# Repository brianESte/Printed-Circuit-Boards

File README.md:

# Printed-Circuit-Boards
A collection of PCBs. Most are interface boards between breadboard and some kind of non-breadboard friendly package.

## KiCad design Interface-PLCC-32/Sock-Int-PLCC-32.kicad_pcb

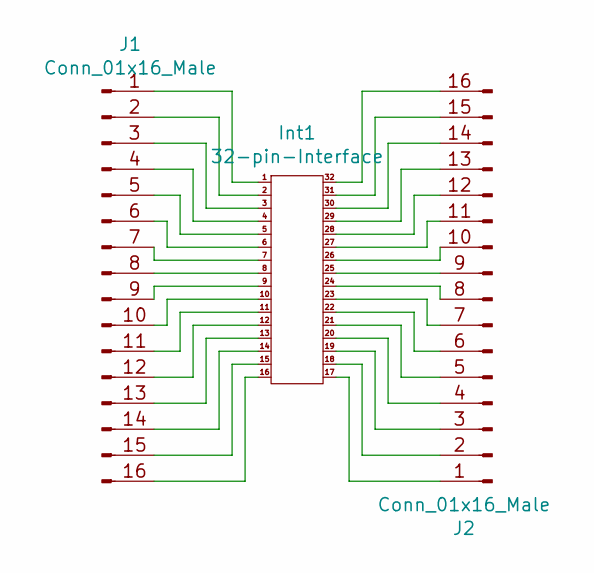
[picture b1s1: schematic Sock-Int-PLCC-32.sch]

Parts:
Int1: 32-pin-Interface; PLCC-Socket-32
J1, J2: Conn_01x16_Male; PinHeader_1x16_P2.54mm_Vertical

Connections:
unnamed: Int1.1, J1.1
unnamed: Int1.2, J1.2
unnamed: Int1.3, J1.3
unnamed: Int1.4, J1.4
unnamed: Int1.5, J1.5
unnamed: Int1.6, J1.6
unnamed: Int1.7, J1.7
unnamed: Int1.8, J1.8
unnamed: Int1.9, J1.9
unnamed: Int1.10, J1.10
unnamed: Int1.11, J1.11
unnamed: Int1.12, J1.12
unnamed: Int1.13, J1.13
unnamed: Int1.14, J1.14
unnamed: Int1.15, J1.15
unnamed: Int1.16, J1.16
unnamed: Int1.17, J2.1
unnamed: Int1.18, J2.2
unnamed: Int1.19, J2.3
unnamed: Int1.20, J2.4
unnamed: Int1.21, J2.5
unnamed: Int1.22, J2.6
unnamed: Int1.23, J2.7
unnamed: Int1.24, J2.8
unnamed: Int1.25, J2.9
unnamed: Int1.26, J2.10
unnamed: Int1.27, J2.11
unnamed: Int1.28, J2.12
unnamed: Int1.29, J2.13
unnamed: Int1.30, J2.14
unnamed: Int1.31, J2.15
unnamed: Int1.32, J2.16

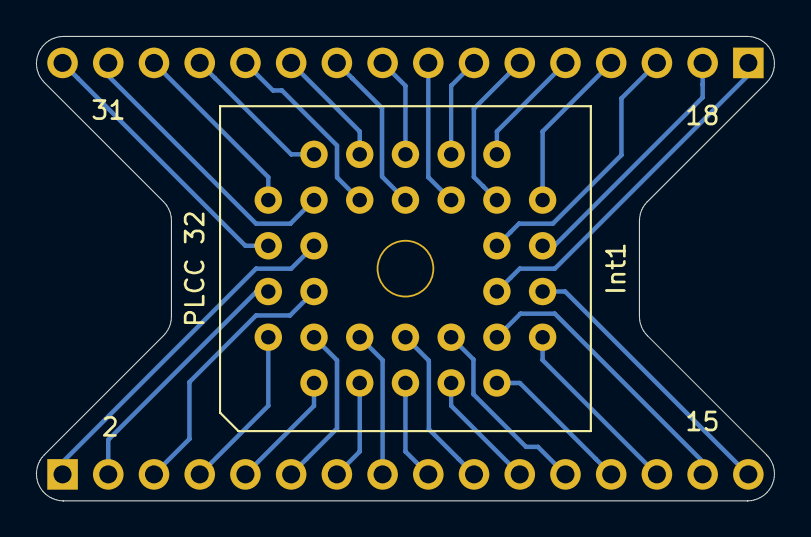
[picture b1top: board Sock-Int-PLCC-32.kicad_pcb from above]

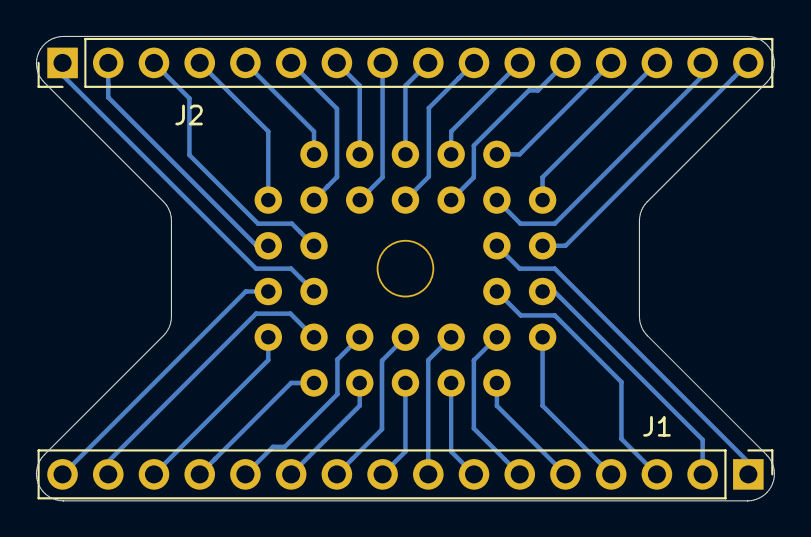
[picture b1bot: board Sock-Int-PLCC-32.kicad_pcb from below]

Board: 2 copper layers, 41.0 x 25.8 mm, 3 parts (2 on the bottom side), 32 nets.

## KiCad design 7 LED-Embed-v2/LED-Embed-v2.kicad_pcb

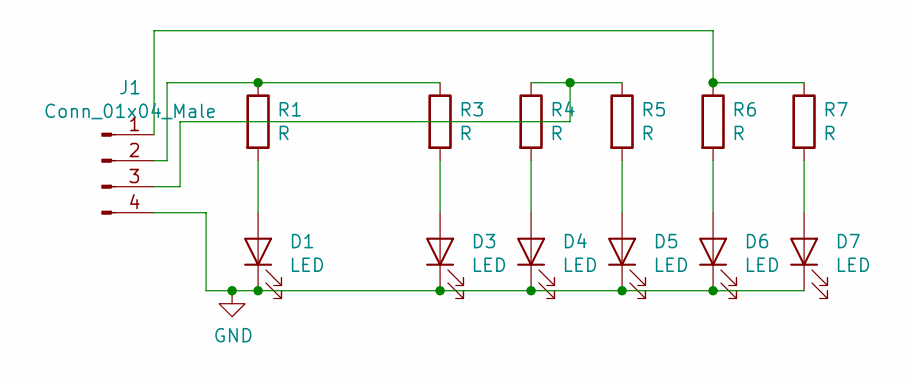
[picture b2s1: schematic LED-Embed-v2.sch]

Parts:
D1: LED; RaisedDome-3.2x1.85
D3: LED; CylLens-3.2x1.1
D4: LED; FlatTop-3.2x0.75
D5, D6: LED; RaisedDome-3.0x2.8
D7: LED; SlantedDome-3.2x1.6
J1: Conn_01x04_Male; PinHeader_1x04_P2.54mm_Vertical
R1, R3, R4, R5, R6, R7: R; R_0805_2012Metric

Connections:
GND: D1.1 (K), D3.1 (K), D4.1 (K), D5.1 (K), D6.1 (K), D7.1 (K), J1.4
unnamed: D1.2 (A), R1.2
unnamed: D3.2 (A), R3.2
unnamed: D4.2 (A), R4.2
unnamed: D5.2 (A), R5.2
unnamed: D6.2 (A), R6.2
unnamed: D7.2 (A), R7.2
unnamed: J1.1, R6.1, R7.1
unnamed: J1.2, R1.1, R3.1
unnamed: J1.3, R4.1, R5.1

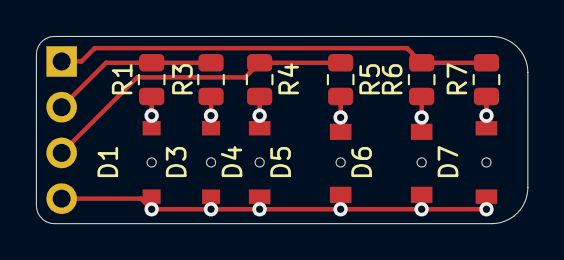
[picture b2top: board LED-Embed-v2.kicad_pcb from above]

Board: 2 copper layers, 27.3 x 10.4 mm, 13 parts (1 on the bottom side), 10 nets.

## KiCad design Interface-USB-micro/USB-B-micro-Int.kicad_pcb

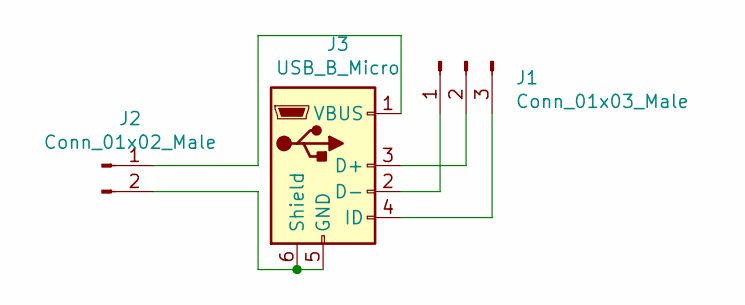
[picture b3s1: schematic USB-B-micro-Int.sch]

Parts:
J1: Conn_01x03_Male; PinHeader_1x03_P2.54mm_Vertical
J2: Conn_01x02_Male; PinHeader_1x02_P2.54mm_Vertical
J3: USB_B_Micro; USB-B-micro-Vert

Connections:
unnamed: J1.1, J3.2 (D-)
unnamed: J1.2, J3.3 (D+)
unnamed: J1.3, J3.4 (ID)
unnamed: J2.1, J3.1 (VBUS)
unnamed: J2.2, J3.5 (GND), J3.6 (Shield)

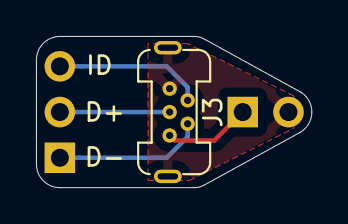
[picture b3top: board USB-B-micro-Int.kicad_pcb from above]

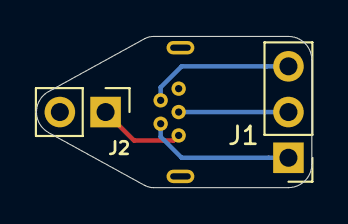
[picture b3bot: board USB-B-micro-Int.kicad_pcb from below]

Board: 2 copper layers, 15.3 x 8.4 mm, 3 parts (2 on the bottom side), 5 nets.

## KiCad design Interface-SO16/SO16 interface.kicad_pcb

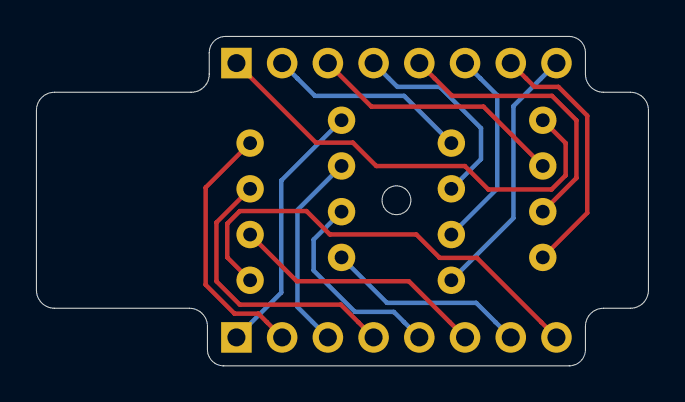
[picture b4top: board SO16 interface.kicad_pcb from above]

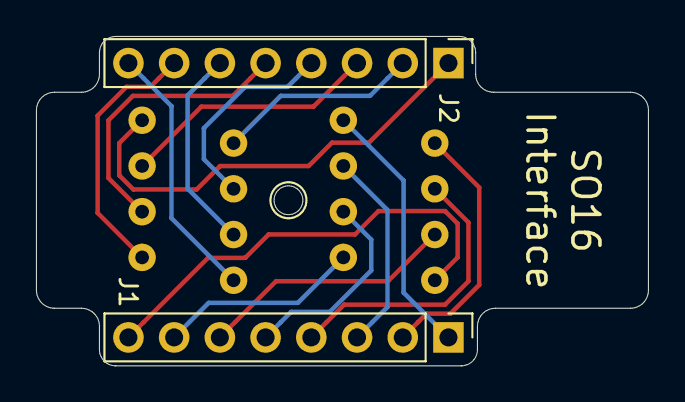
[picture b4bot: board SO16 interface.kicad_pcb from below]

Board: 2 copper layers, 34.0 x 18.3 mm, 3 parts (2 on the bottom side), 16 nets.

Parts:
Conn1: SO16; SO16-7383
J1, J2: Conn_01x08_Male; PinHeader_1x08_P2.54mm_Vertical

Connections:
unnamed: Conn1.1, J1.1
unnamed: Conn1.2, J1.2
unnamed: Conn1.3, J1.3
unnamed: Conn1.4, J1.4
unnamed: Conn1.5, J1.5
unnamed: Conn1.6, J1.6
unnamed: Conn1.7, J1.7
unnamed: Conn1.8, J1.8
unnamed: Conn1.9, J2.8
unnamed: Conn1.10, J2.7
unnamed: Conn1.11, J2.6
unnamed: Conn1.12, J2.5
unnamed: Conn1.13, J2.4
unnamed: Conn1.14, J2.3
unnamed: Conn1.15, J2.2
unnamed: Conn1.16, J2.1

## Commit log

2020-07-25 initializing repository
2020-07-25 remove unwanted folder
2020-07-25 update READMEs
